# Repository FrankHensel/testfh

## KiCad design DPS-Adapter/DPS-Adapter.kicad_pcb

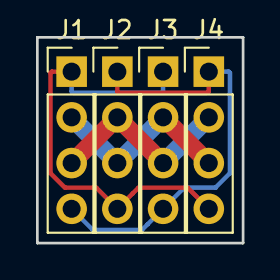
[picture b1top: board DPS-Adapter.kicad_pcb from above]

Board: 2 copper layers, 11.4 x 11.4 mm, 4 parts (0 on the bottom side), 4 nets.

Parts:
J1, J2, J3, J4: Conn_01x04; Socket_Strip_Straight_1x04_Pitch2.54mm

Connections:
/F: J1.3, J2.2, J3.3, J4.2
/FS: J1.1, J2.4, J3.1, J4.4
/GND: J1.2, J2.3, J3.2, J4.3
/GS: J1.4, J2.1, J3.4, J4.1

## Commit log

2018-03-11 add new project sbout some adapter
2018-03-11 started with design of PCB Layout
2018-03-11 adapter finally routed
2018-05-01 populate changes to archive correct version
2018-08-18 transition test to 5
